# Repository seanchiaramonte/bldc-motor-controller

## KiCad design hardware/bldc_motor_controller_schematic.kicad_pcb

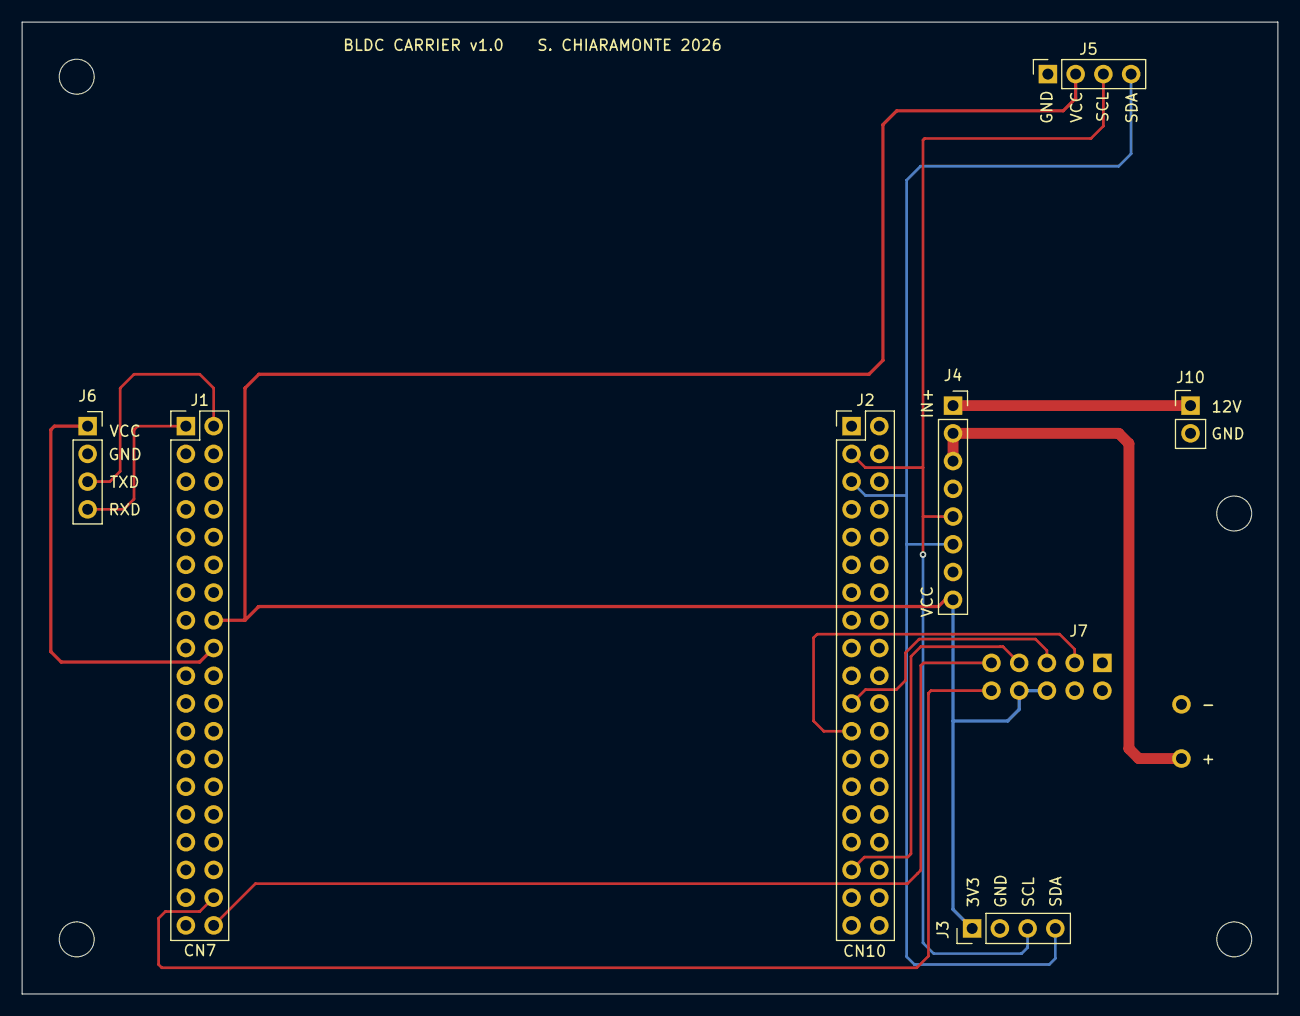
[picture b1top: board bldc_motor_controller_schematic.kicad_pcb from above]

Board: 2 copper layers, 115.0 x 89.0 mm, 12 parts (0 on the bottom side), 14 nets.

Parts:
H1, H2, H3, H4: MountingHole_3.2mm_M3
J1, J2: Conn_02x19_Odd_Even; PinHeader_2x19_P2.54mm_Vertical
J3: J_AS5600; PinHeader_1x04_P2.54mm_Vertical
J4: J_INA226; PinSocket_1x08_P2.54mm_Vertical
J5: J_SSD1306; PinSocket_1x04_P2.54mm_Vertical
J6: J_HM10; PinSocket_1x04_P2.54mm_Vertical
J7: J_DRV8313_CTRL; SimpleFOC_Mini_v1
J10: J_BARREL_JACK1; PinHeader_1x02_P2.54mm_Vertical

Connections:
+3V3: J1.16 (3V3), J3.1 (VCC), J4.8 (VCC), J5.2 (VCC), J7.8 (nSP), J7.9 (nRT)
+5V: J1.18 (5V), J6.1 (VCC)
+12V: J4.1 (IN+), J10.1 (+)
/EN: J1.38 (PC0), J7.6 (EN)
/PWM_IN1: J2.23 (PA8), J7.3 (IN1)
/PWM_IN2: J2.21 (PA9), J7.4 (IN2)
/PWM_IN3: J2.33 (PA10), J7.5 (IN3)
/SCL: J2.3 (PB8), J3.3 (SCL), J4.5 (SCL), J5.3 (SCL)
/SDA: J2.5 (PB9), J3.4 (SDA), J4.6 (SDA), J5.4 (SDA)
/UART_RX: J1.2 (PC11), J6.3 (TXD)
/UART_TX: J1.1 (PC10), J6.4 (RXD)
/VM: J4.2 (IN-), J4.3 (VBS), J7.1 (+)
/nFT: J1.36 (PC1), J7.7 (nFT)
GND: J1.8 (GND), J1.19 (GND), J1.20 (GND), J1.22 (GND), J2.9 (GND), J2.20 (GND), J3.2 (GND), J4.7 (GND), J5.1 (GND), J6.2 (GND), J7.2 (-), J7.10 (GND), J7.11 (GND), J10.2 (-)
